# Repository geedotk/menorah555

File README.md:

# Menorah555

Menorah555 is an LED menorah that uses flickering LEDs to simulate the candles.
The shamash (helper candle) is removed and used to "light" the other candles.

## Circuit:
The menorah is built around LEDs that look like standard 5-mm LEDs (T-1 3/4), but
they actually have a chip inside that applies PWM to the LED to simulate a 
flickering flame. This means that no special driver circuitry is needed to create
that effect. Thus, the circuit has no microcontroller in it.

The shamash "candle" has a single flickering LED driven with a super cap. The shamash
board is a daughter board that can be unplugged, and the super cap will allow the
LED to keep lit for a while. A current limiter circuit keeps the inrush current down
so that charging the super cap does not cause the power supply to trip the current limit.

The "candle" lighting circuits are built around 555 timers. This could have been done
with fewer parts in a number of ways, but the 555 was selected to silence the
pundits that say, "it could have been done with a 555!" The 555 on each candle is used as
a set-reset flip-flop. Another 555 timer is configured to provide a power-on reset to
ensure that all LEDs (except for the shamash) are unlit when power is turned on. Triggering
of the 555 to turn on the LED is done with a reed switch. The shamash PCB has a magnet
mounted on it to trigger the reed switch and "light" the candle.

## PCB
Schematic capture and PCB layout were done in [KiCad](https://www.kicad.org/) 6.0.0.
There is no problem fitting everything on the PCB because the size is dictated more
by the aesthetics than the component size. In fact, the electrolytic capacitors selected
are MUCH larger than necessary because they are part of the suggestion of a candle shape.

## Base
The base of the menorah was designed in [FreeCAD](https://www.freecadweb.org/) 0.19 and
was designed to be made of acrylic or similar plastic and bent to the proper final
shape. It's not always easy to be consistent in heat-bending acrylic, so it may be better
to drill the mounting holes after bending. Otherwise, the base may not sit flat on a table.

## Flame Diffusors
The flame diffusors were designed in FreeCAD and were meant to be FDM printed in transparent
filament. The layer lines and in-fill will help to diffuse the light.

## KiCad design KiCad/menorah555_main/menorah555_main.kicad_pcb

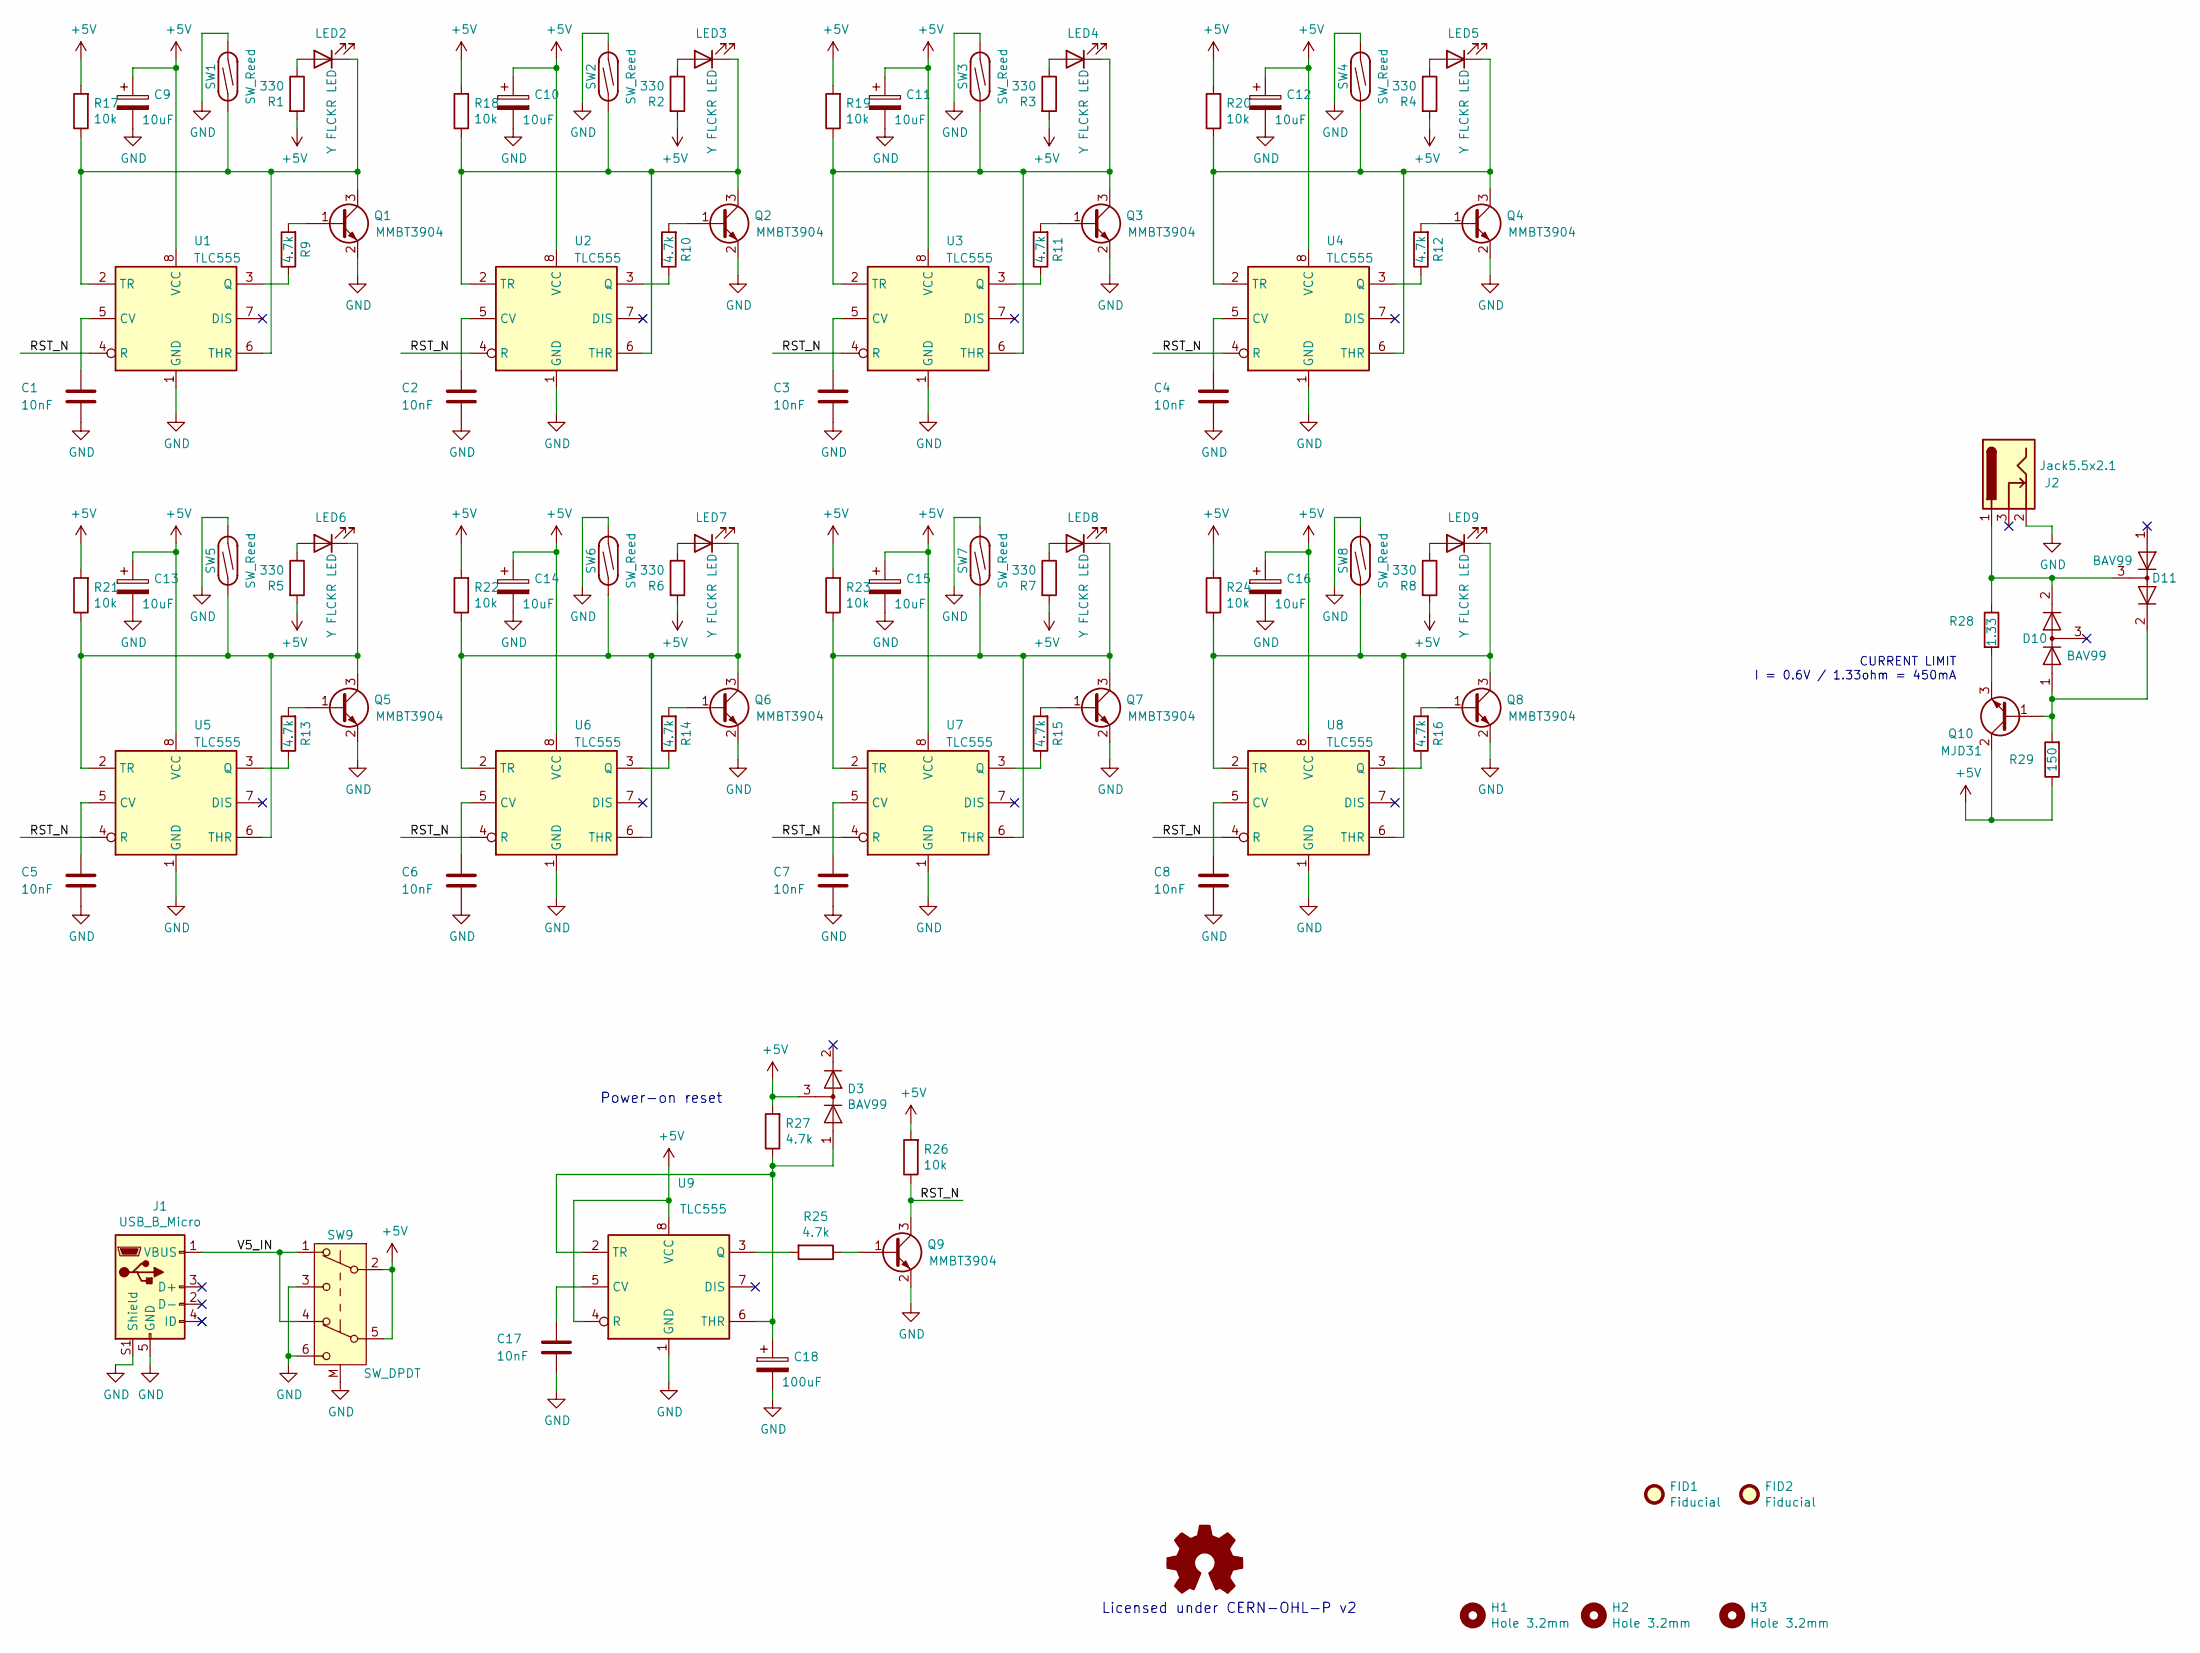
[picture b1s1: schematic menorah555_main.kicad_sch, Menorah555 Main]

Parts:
C1, C2, C3, C4, C5, C6, C7, C8, C17: 10nF; C_0805_2012Metric
C9, C10, C11, C12, C13, C14, C15, C16: 10uF; CP_Radial_Horizontal_D8.0mm_L12.0mm_P3.50mm
C18: 100uF; CP_Radial_Horizontal_D5.0mm_H11.0mm_P2.00mm
D3, D10, D11: BAV99; SOT-23
FID1, FID2: Fiducial; Fiducial_1mm_Mask2mm
H1, H2, H3: Hole 3.2mm; MountingHole_3.2mm_M3
J1: USB_B_Micro; AMPHENOL_10118194-0001LF
J2: Jack5.5x2.1; Gravitech_CONSOCJ2155_2.1mm_5.5mm_Barrel_Jack_Z2.35
LED2, LED3, LED4, LED5, LED6, LED7, LED8, LED9: Y FLCKR LED; LED_D5.0mm_Horizontal_SMT_O3.81mm
LOGO2: Logo_Open_Hardware_Small; OSHW-Logo2_9.8x8mm_SilkScreen
Q1, Q2, Q3, Q4, Q5, Q6, Q7, Q8, Q9: MMBT3904; SOT-23
Q10: MJD31; TO-252-2
R1, R2, R3, R4, R5, R6, R7, R8: 330; R_0805_2012Metric
R9, R10, R11, R12, R13, R14, R15, R16, R25, R27: 4.7k; R_0805_2012Metric
R17, R18, R19, R20, R21, R22, R23, R24, R26: 10k; R_0805_2012Metric
R28: 1.33; R_2010_5025Metric
R29: 150; R_0805_2012Metric
SW1, SW2, SW3, SW4, SW5, SW6, SW7, SW8: SW_Reed; SW_SPST_REED_59170-1-S-00-D
SW9: SW_DPDT; SW_Nidec_MFS201N-9-Z_DPDT_Straight
U1, U2, U3, U4, U5, U6, U7, U8, U9: TLC555; SOIC-8_3.9x4.9mm_P1.27mm

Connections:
+5V: C9.1, C10.1, C11.1, C12.1, C13.1, C14.1, C15.1, C16.1, D3.3 (K), Q10.2 (C), R1.2, R2.2, R3.2, R4.2, R5.2, R6.2, R7.2, R8.2, R17.2, R18.2, R19.2, R20.2, R21.2, R22.2, R23.2, R24.2, R26.2, R27.2, R29.1, SW9.2 (B), SW9.5 (B), U1.8 (VCC), U2.8 (VCC), U3.8 (VCC), U4.8 (VCC), U5.8 (VCC), U6.8 (VCC), U7.8 (VCC), U8.8 (VCC), U9.4 (R), U9.8 (VCC)
/RST_N: Q9.3 (C), R26.1, U1.4 (R), U2.4 (R), U3.4 (R), U4.4 (R), U5.4 (R), U6.4 (R), U7.4 (R), U8.4 (R)
/V5_IN: J1.1 (VBUS), SW9.1 (A), SW9.4 (A)
GND: C1.2, C2.2, C3.2, C4.2, C5.2, C6.2, C7.2, C8.2, C9.2, C10.2, C11.2, C12.2, C13.2, C14.2, C15.2, C16.2, C17.2, C18.2, J1.5 (GND), J1.S1 (Shield), J1.S2 (Shield), J1.S3 (Shield), J1.S4 (Shield), J1.S5 (Shield), J1.S6 (Shield), J2.2, Q1.2 (E), Q2.2 (E), Q3.2 (E), Q4.2 (E), Q5.2 (E), Q6.2 (E), Q7.2 (E), Q8.2 (E), Q9.2 (E), SW1.2, SW2.2, SW3.2, SW4.2, SW5.2, SW6.2, SW7.2, SW8.2, SW9.3 (C), SW9.6 (C), SW9.M, U1.1 (GND), U2.1 (GND), U3.1 (GND), U4.1 (GND), U5.1 (GND), U6.1 (GND), U7.1 (GND), U8.1 (GND), U9.1 (GND)
unnamed: C1.1, U1.5 (CV)
unnamed: C2.1, U2.5 (CV)
unnamed: C3.1, U3.5 (CV)
unnamed: C4.1, U4.5 (CV)
unnamed: C5.1, U5.5 (CV)
unnamed: C6.1, U6.5 (CV)
unnamed: C7.1, U7.5 (CV)
unnamed: C8.1, U8.5 (CV)
unnamed: C17.1, U9.5 (CV)
unnamed: C18.1, D3.1 (K), R27.1, U9.2 (TR), U9.6 (THR)
unnamed: D10.1 (K), D11.2 (A), Q10.1 (B), R29.2
unnamed: D10.2 (A), D11.3 (K), J2.1, R28.1
unnamed: LED2.1 (K), Q1.3 (C), R17.1, SW1.1, U1.2 (TR), U1.6 (THR)
unnamed: LED2.2 (A), R1.1
unnamed: LED3.1 (K), Q2.3 (C), R18.1, SW2.1, U2.2 (TR), U2.6 (THR)
unnamed: LED3.2 (A), R2.1
unnamed: LED4.1 (K), Q3.3 (C), R19.1, SW3.1, U3.2 (TR), U3.6 (THR)
unnamed: LED4.2 (A), R3.1
unnamed: LED5.1 (K), Q4.3 (C), R20.1, SW4.1, U4.2 (TR), U4.6 (THR)
unnamed: LED5.2 (A), R4.1
unnamed: LED6.1 (K), Q5.3 (C), R21.1, SW5.1, U5.2 (TR), U5.6 (THR)
unnamed: LED6.2 (A), R5.1
unnamed: LED7.1 (K), Q6.3 (C), R22.1, SW6.1, U6.2 (TR), U6.6 (THR)
unnamed: LED7.2 (A), R6.1
unnamed: LED8.1 (K), Q7.3 (C), R23.1, SW7.1, U7.2 (TR), U7.6 (THR)
unnamed: LED8.2 (A), R7.1
unnamed: LED9.1 (K), Q8.3 (C), R24.1, SW8.1, U8.2 (TR), U8.6 (THR)
unnamed: LED9.2 (A), R8.1
unnamed: Q1.1 (B), R9.2
unnamed: Q2.1 (B), R10.2
unnamed: Q3.1 (B), R11.2
unnamed: Q4.1 (B), R12.2
unnamed: Q5.1 (B), R13.2
unnamed: Q6.1 (B), R14.2
unnamed: Q7.1 (B), R15.2
unnamed: Q8.1 (B), R16.2
unnamed: Q9.1 (B), R25.1
unnamed: Q10.3 (E), R28.2
unnamed: R9.1, U1.3 (Q)
unnamed: R10.1, U2.3 (Q)
unnamed: R11.1, U3.3 (Q)
unnamed: R12.1, U4.3 (Q)
unnamed: R13.1, U5.3 (Q)
unnamed: R14.1, U6.3 (Q)
unnamed: R15.1, U7.3 (Q)
unnamed: R16.1, U8.3 (Q)
unnamed: R25.2, U9.3 (Q)

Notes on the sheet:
Power-on reset
CURRENT LIMIT I = 0.6V / 1.33ohm = 450mA
Licensed under CERN-OHL-P v2

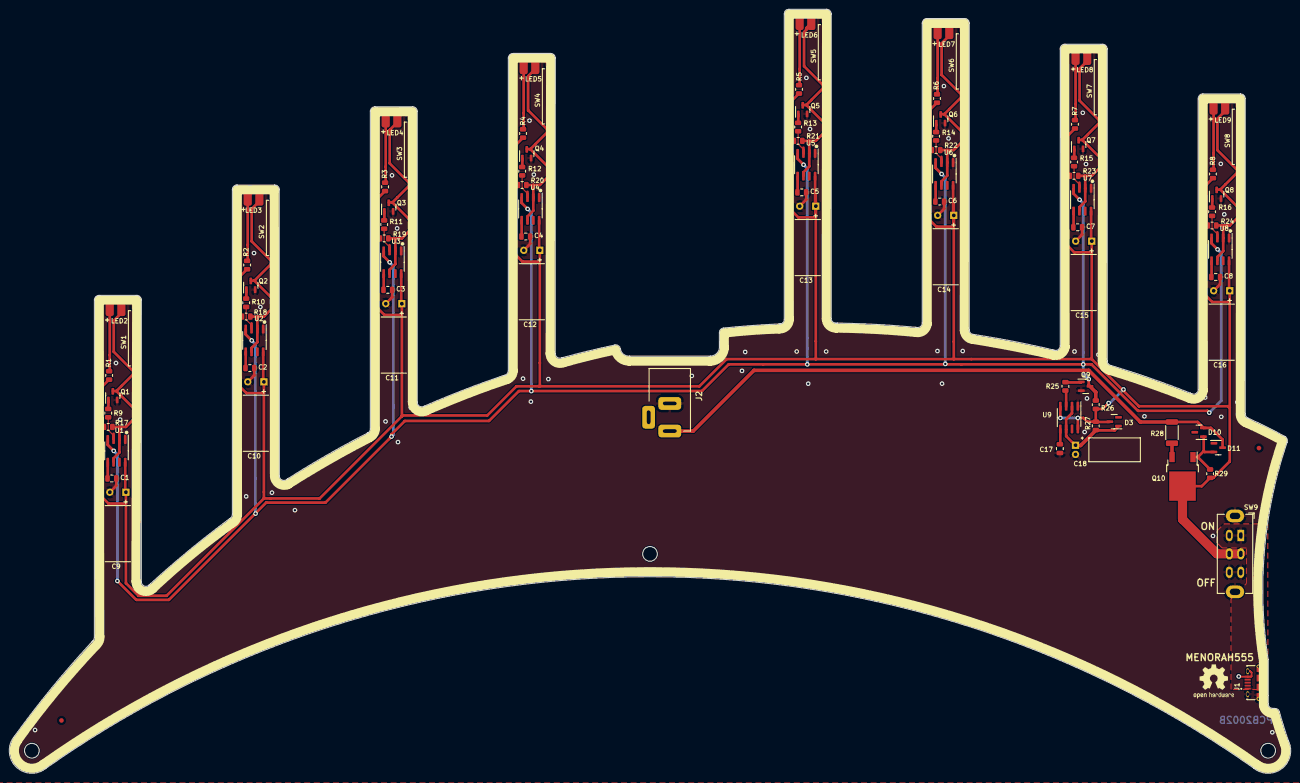
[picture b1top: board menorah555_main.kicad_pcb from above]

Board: 2 copper layers, 278.6 x 166.1 mm, 94 parts (0 on the bottom side), 51 nets.

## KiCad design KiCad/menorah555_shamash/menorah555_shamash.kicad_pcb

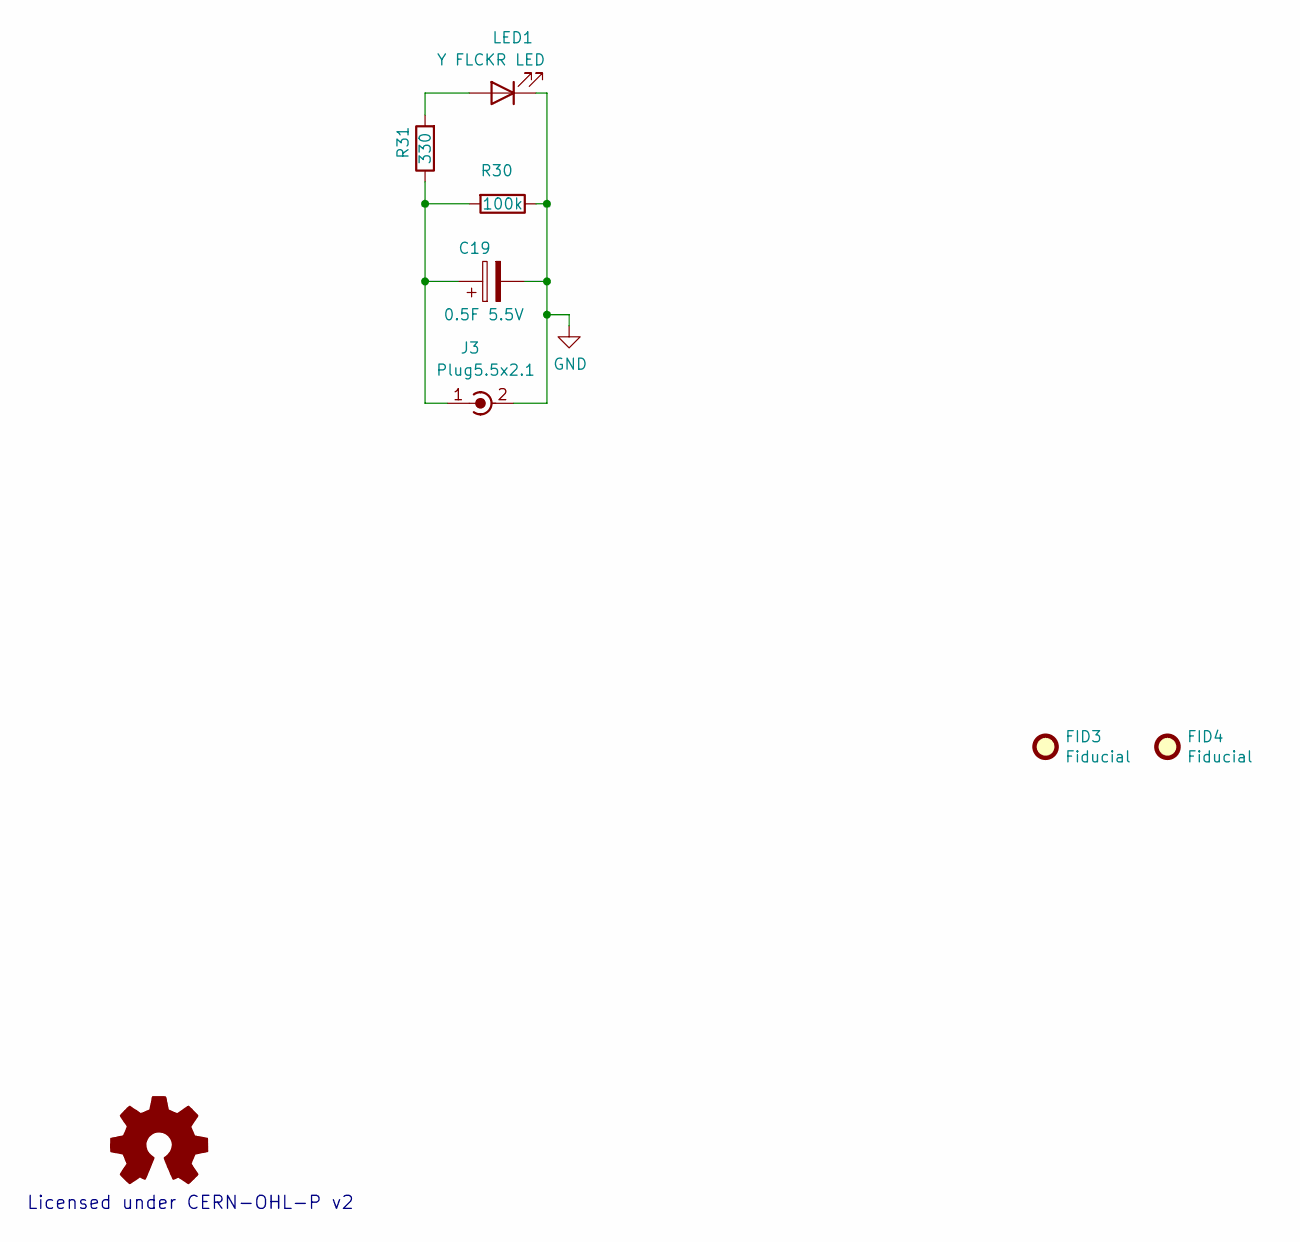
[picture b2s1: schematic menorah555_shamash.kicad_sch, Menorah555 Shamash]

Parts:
C19: 0.5F 5.5V; CP_Supercap_DGH504Q5R5_Horizontal
FID3, FID4: Fiducial; Fiducial_1mm_Mask2mm
J3: Plug5.5x2.1; KobiConn_173-5521TIP-EX_power_plug
LED1: Y FLCKR LED; LED_D5.0mm_Horizontal_SMT_O3.81mm
LOGO2: Logo_Open_Hardware_Small; OSHW-Logo2_9.8x8mm_SilkScreen
R30: 100k; R_0805_2012Metric
R31: 330; R_0805_2012Metric

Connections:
GND: C19.2, J3.2 (Ext), LED1.1 (K), R30.1
unnamed: C19.1, J3.1 (In), R30.2, R31.1
unnamed: LED1.2 (A), R31.2

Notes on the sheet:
Licensed under CERN-OHL-P v2

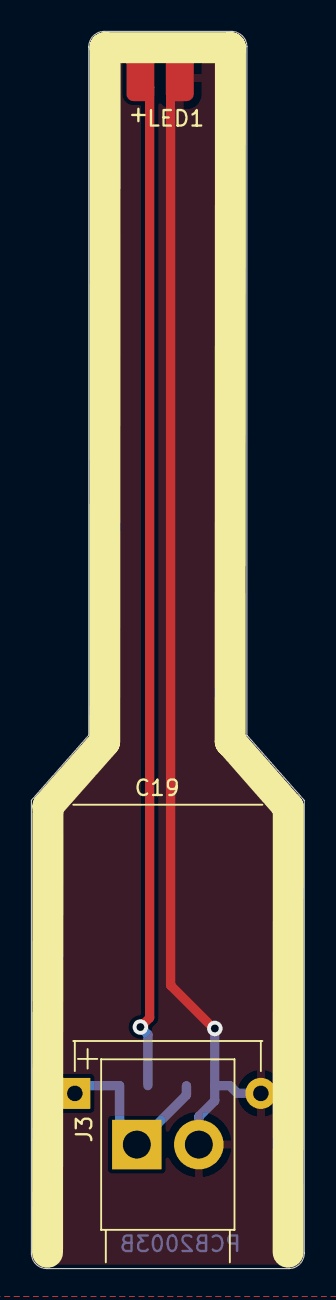
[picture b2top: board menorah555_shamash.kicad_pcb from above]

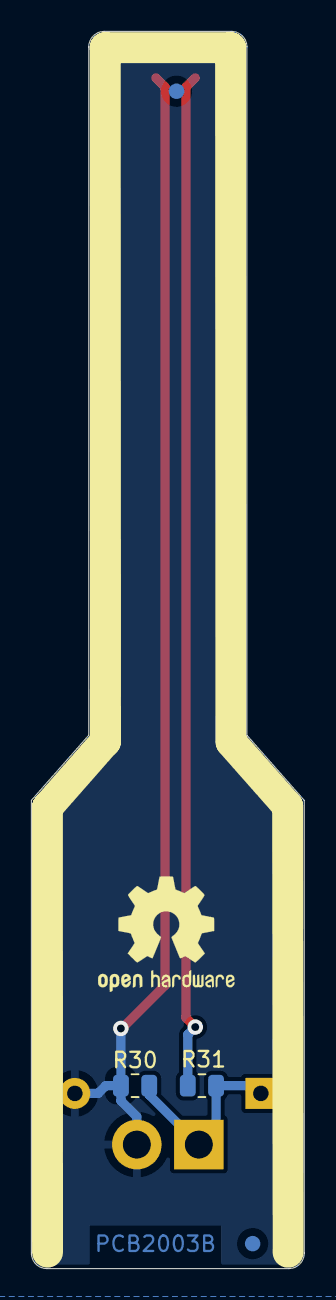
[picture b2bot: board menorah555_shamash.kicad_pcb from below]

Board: 2 copper layers, 17.6 x 79.8 mm, 8 parts (5 on the bottom side), 3 nets.

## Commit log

2021-12-04 Initial version of the menorah555 project
    This contains the KiCad schematics and PCB files, as well as the FreeCAD models of
    the base and flame diffusers.
2021-12-30 Renamed directory
    The menorah PCB will be split into separate designs for the main board
    and for the shamash, so the directory is renamed as a step toward doing
    this
2022-01-02 Updated design to KiCad 6.0.0
    Initially the design was created in KiCad 5.1.12. To update it to KiCad
    6.0.0 the path for the 3d models had to be changed from KISYS3DMOD to
    KICAD6_3DMODEL_DIR. Additionally, the .wrl file were all changed to
    .step files. No functional changes to the schematic or PCB were done
    when updating to KiCad 6
2022-01-03 Split PCB into separate main and shamash boards
    Previously, the main and shamash PCBs were combined into one file.
    Now they are separate PCBs so that they don't need to be cut apart and
    smoothed.
2022-01-03 Fixed long turn-off time
    Previously on the rev A PCB (PCB2002A), when power was turned off, the
    shamash would take a very long time (> 20 minutes) to fully turn off.
    Now a new diode, D11, has been added to drain the supercap when power is
    turned off with the switch.
2022-01-03 Made USB footprint hand-solderable
    The USB footprint was changed to be an Amphenol 10118194-0001LF so that
    it could be hand-soldered if desired.
2022-01-03 Eliminated silkscreen crossing edge cuts
    The DRC was giving warnings for silkscreen that overlapped with edge
    cuts because it was getting cut by the soldermask. The footprints for
    the LEDs and the shamash power connector were updated to delete the
    silkscreen outside of the board edge cuts
2022-01-03 Offset the J2 model in Z direction
    The 3d model for the J2 power jack has been offset by 2.35mm so that it
    will make the main PCB and shamash PCB line up.
2022-01-04 Updated slide switch to ground the case
    The Nidec slide switch case had pins named 'M' that were not on the
    schematic, so they did not get connected on the PCB. Now those pins have
    been added to the symbol and connected to ground.
2022-02-20 Added silkscreen 2mm stripe at edge
    For aesthetic reasons, a 2mm silkscreen strip was added around the board
    on top and bottom. Gerbers were also generated
2022-03-07 Removed unused layers
    There are no components on the bottom side, so there is no need for the
    bottom fab or bottom paste layers
2022-03-07 Added alignment holes to paste layer
    In order to facilitate hand stenciling solder paste onto the board,
    holes have been added to the front paste layer that align with two
    mounting holes.
